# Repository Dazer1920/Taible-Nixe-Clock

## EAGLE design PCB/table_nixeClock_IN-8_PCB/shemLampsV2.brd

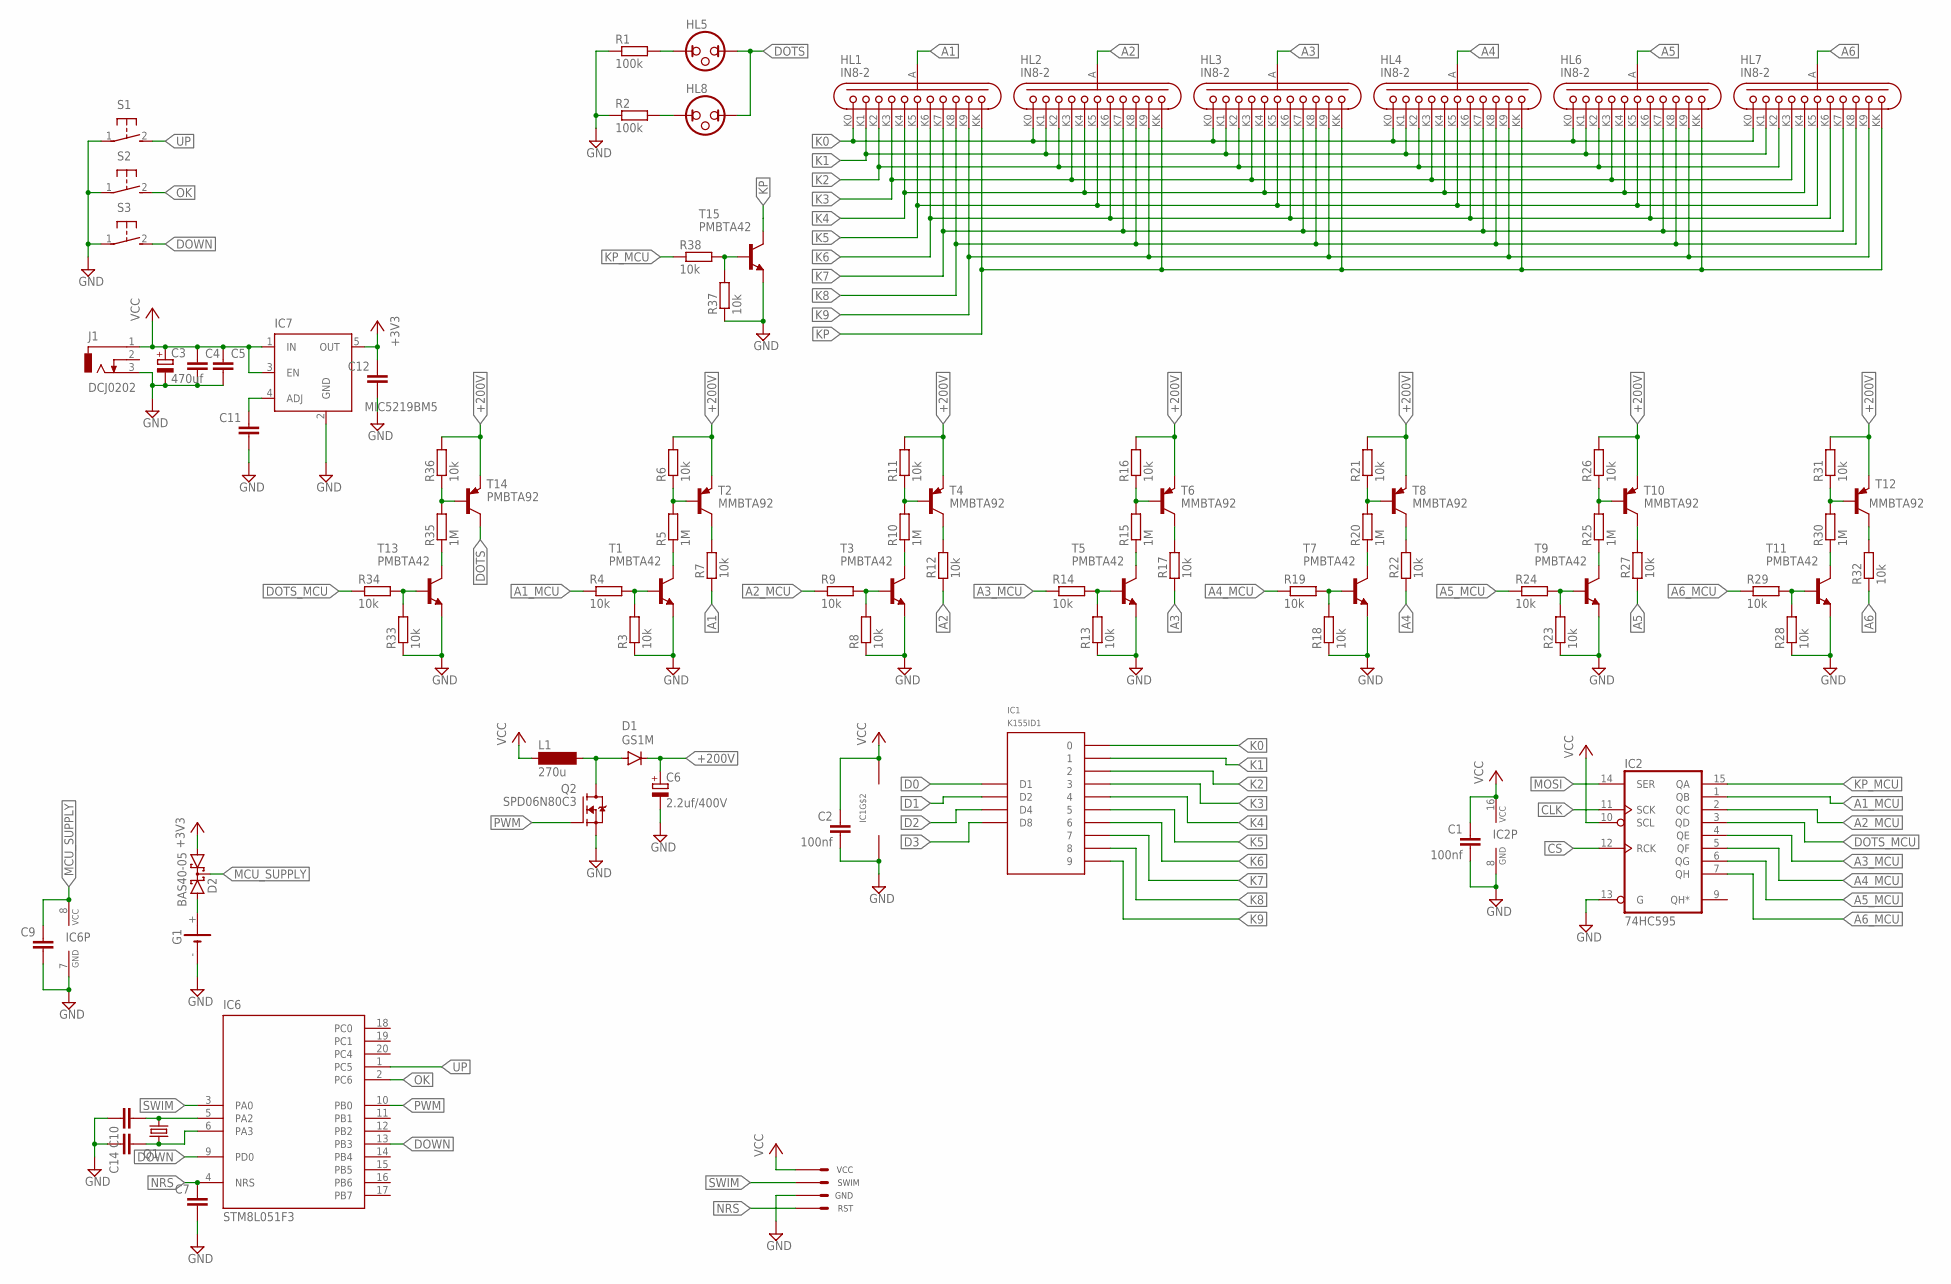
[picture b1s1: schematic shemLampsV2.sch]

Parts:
C1, C2: 100nf; C0805
C3: 470uf; E3,5-8
C4, C5, C7, C9, C10, C11, C12, C14: C0805; CAPC2113X70
C6: 2.2uf/400V; E3,5-8
D1: GS1M; DO-214AC
D2: BAS40-05; SOT23
G1: BATTERY; CH291-1220LF_W
HL1, HL2, HL3, HL4, HL6, HL7: IN8-2
HL5, HL8: NEON_LAMP
IC1: K155ID1; DIL16
IC2: 74HC595; TSSOP16L
IC6: STM8L051F3; TSSOP-20
IC7: MIC5219BM5; SOT23-5
J1: DCJ0202
L1: 270u; BS11
Q1: FC-12M
Q2: SPD06N80C3; TO252
R1, R2: 100k; 0207/10
R3, R4, R6, R7, R8, R9, R11, R12, R13, R14, R16, R17, R18, R19, R21, R22, R23, R24, R26, R27, R28, R29, R31, R32, R33, R34, R36, R37, R38: 10k; R0805
R5, R10, R15, R20, R25, R30, R35: 1M; R0805
S1, S2, S3: 31-XX; B3F-31XX
SV1: SWIM
T1, T3, T5, T7, T9, T11, T13, T15: PMBTA42; SOT23-BEC
T2, T4, T6, T8, T10, T12: MMBTA92; SOT23-BEC
T14: PMBTA92; SOT23-BEC

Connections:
+3V3: C12.1, D2.1 (A1), IC7.5 (OUT)
+200V: C6.+, D1.C, R6.2, R11.2, R16.2, R21.2, R26.2, R31.2, R36.2, T2.E, T4.E, T6.E, T8.E, T10.E, T12.E, T14.E
A1: HL1.A, R7.1
A1_MCU: IC2.1 (QB), R4.1
A2: HL2.A, R12.1
A2_MCU: IC2.2 (QC), R9.1
A3: HL3.A, R17.1
A3_MCU: IC2.4 (QE), R14.1
A4: HL4.A, R22.1
A4_MCU: IC2.5 (QF), R19.1
A5: HL6.A, R27.1
A5_MCU: IC2.6 (QG), R24.1
A6: HL7.A, R32.1
A6_MCU: IC2.7 (QH), R29.1
CLK: IC2.11 (SCK)
CS: IC2.12 (RCK)
D0: IC1.3 (D1)
D1: IC1.6 (D2)
D2: IC1.7 (D4)
D3: IC1.4 (D8)
DOTS: HL5.2, HL8.2, T14.C
DOTS_MCU: IC2.3 (QD), R34.1
DOWN: IC6.9 (PD0), IC6.13 (PB3), S3.2 (S)
GND: C1.2, C2.2, C3.-, C4.2, C5.2, C6.-, C7.2, C9.2, C10.1, C11.2, C12.2, C14.1, G1.-, IC1.12 (GND), IC2.8 (GND), IC2.13 (G), IC6.7 (GND), IC7.2 (GND), J1.3, Q2.2 (S), R1.1, R2.1, R3.1, R8.1, R13.1, R18.1, R23.1, R28.1, R33.1, R37.1, S1.1, S2.1, S3.1, SV1.GND, T1.E, T3.E, T5.E, T7.E, T9.E, T11.E, T13.E, T15.E
K0: HL1.K0, HL2.K0, HL3.K0, HL4.K0, HL6.K0, HL7.K0, IC1.16 (0)
K1: HL1.K1, HL2.K1, HL3.K1, HL4.K1, HL6.K1, HL7.K1, IC1.15 (1)
K2: HL1.K2, HL2.K2, HL3.K2, HL4.K2, HL6.K2, HL7.K2, IC1.8 (2)
K3: HL1.K3, HL2.K3, HL3.K3, HL4.K3, HL6.K3, HL7.K3, IC1.9 (3)
K4: HL1.K4, HL2.K4, HL3.K4, HL4.K4, HL6.K4, HL7.K4, IC1.13 (4)
K5: HL1.K5, HL2.K5, HL3.K5, HL4.K5, HL6.K5, HL7.K5, IC1.14 (5)
K6: HL1.K6, HL2.K6, HL3.K6, HL4.K6, HL6.K6, HL7.K6, IC1.11 (6)
K7: HL1.K7, HL2.K7, HL3.K7, HL4.K7, HL6.K7, HL7.K7, IC1.10 (7)
K8: HL1.K8, HL2.K8, HL3.K8, HL4.K8, HL6.K8, HL7.K8, IC1.1 (8)
K9: HL1.K9, HL2.K9, HL3.K9, HL4.K9, HL6.K9, HL7.K9, IC1.2 (9)
KP: HL1.KK, HL2.KK, HL3.KK, HL4.KK, HL6.KK, HL7.KK, T15.C
KP_MCU: IC2.15 (QA), R38.1
MCU_SUPPLY: C9.1, D2.3 (C), IC6.8 (VCC)
MOSI: IC2.14 (SER)
unnamed: HL5.1, R1.2
unnamed: HL8.1, R2.2
unnamed: R3.2, R4.2, T1.B
unnamed: R8.2, R9.2, T3.B
unnamed: R5.1, T1.C
unnamed: R5.2, R6.1, T2.B
unnamed: R10.1, T3.C
unnamed: R7.2, T2.C
unnamed: R10.2, R11.1, T4.B
unnamed: R12.2, T4.C
unnamed: R13.2, R14.2, T5.B
unnamed: R15.1, T5.C
unnamed: R15.2, R16.1, T6.B
unnamed: R17.2, T6.C
unnamed: R18.2, R19.2, T7.B
unnamed: R20.1, T7.C
unnamed: R20.2, R21.1, T8.B
unnamed: R22.2, T8.C
unnamed: R23.2, R24.2, T9.B
unnamed: R25.1, T9.C
unnamed: R25.2, R26.1, T10.B
unnamed: R27.2, T10.C
unnamed: R28.2, R29.2, T11.B
unnamed: R30.1, T11.C
unnamed: R30.2, R31.1, T12.B
unnamed: R32.2, T12.C
unnamed: R37.2, R38.2, T15.B
unnamed: D1.A, L1.2, Q2.3 (D)
unnamed: C14.2, IC6.6 (PA3), Q1.1
unnamed: C10.2, IC6.5 (PA2), Q1.2
unnamed: D2.2 (A2), G1.+
unnamed: C11.1, IC7.4 (ADJ)
unnamed: R33.2, R34.2, T13.B
unnamed: R35.1, T13.C
unnamed: R35.2, R36.1, T14.B
NRS: C7.1, IC6.4 (NRS), SV1.NRS (RST)
OK: IC6.2 (PC6), S2.2 (S)
PWM: IC6.10 (PB0), Q2.1 (G)
SWIM: IC6.3 (PA0), SV1.SWIM
UP: IC6.1 (PC5), S1.2 (S)
VCC: C1.1, C2.1, C3.+, C4.1, C5.1, IC1.5 (VCC), IC2.10 (SCL), IC2.16 (VCC), IC7.1 (IN), IC7.3 (EN), J1.1, L1.1, SV1.VCC

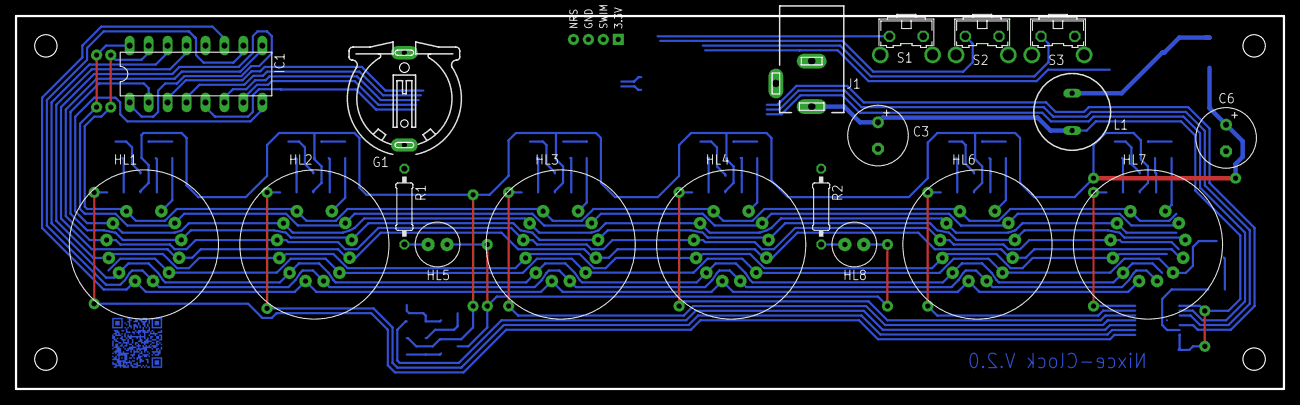
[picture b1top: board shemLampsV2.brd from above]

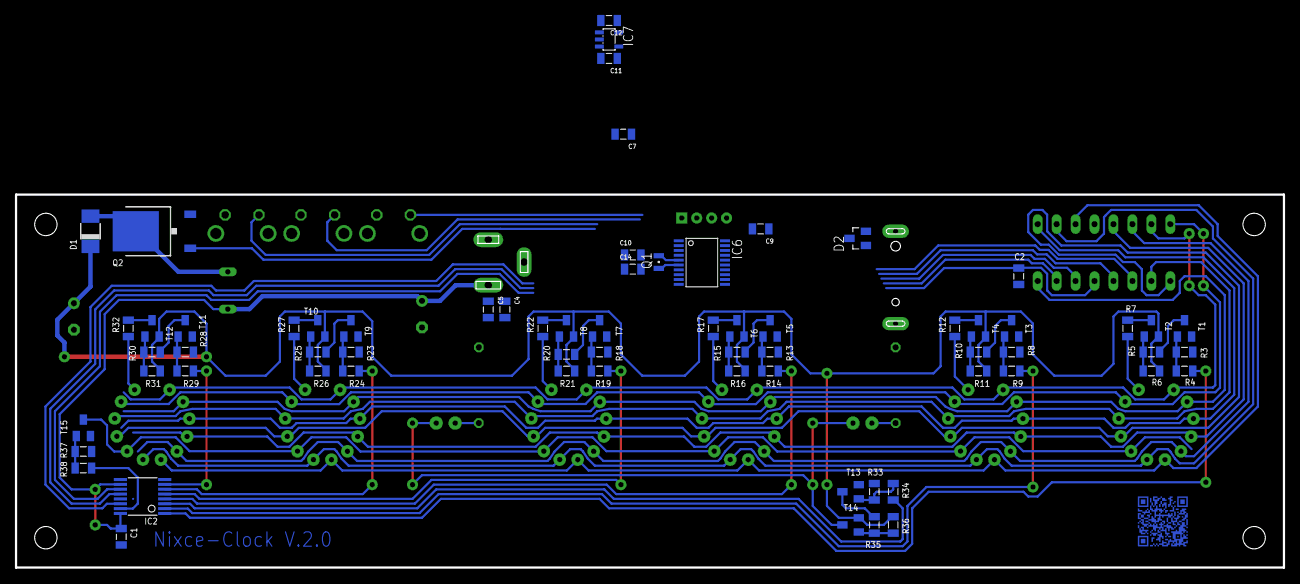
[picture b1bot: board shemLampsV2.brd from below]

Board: 2 copper layers, 170.0 x 50.0 mm, 88 parts (68 on the bottom side), 72 nets.

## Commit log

2020-07-14 Realese V2
2020-07-14 realease V2.2
2020-07-14 RealeaseV2.2
2020-07-15 RealeaseV2
2020-07-29 Realease V2.2
    fixed freeze on i2c crashes
2020-09-07 NewRealease
